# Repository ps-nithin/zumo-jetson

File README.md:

# zumo-jetson

A robot that learns and recognizes patterns on the go.

1. The robot is based on Jetson Nano.

2. The demo script reads the camera frames. Masks the blob, here green (for recognizing) and blue (for learning), using color based segmentation by converting the frames to HSV color space. A check is applied to avoid blobs overlapping with the edge of the frame. The masked image is then inputted to pyrebel which learns/recognizes the blob (using https://github.com/ps-nithin/pyrebel#5-pattern-recognition-demo). Here the recognized symbols are mapped with audio recordings made during learning the pattern. The recorded audio is played back during recognition.

3. The robot uses an Arduino Nano RP2040 Connect as motor controller. It is connected to jetson nano over usb. The arduino firmware has common functions to drive motors and leds connected to it. For example, sending "blinkledwhite_1" over serial to the arduino turns on the white led.

4. Three leds (white, green and blue) connected to the arduino shows the current state of the program. The white led blinks when the program is ready to accept input. The green led blinks when a green blob is detected in the input and the program tries to recognize the input. The blue led blinks when a blue blob is detected in the input and the program tries to learn the input. When both the green and the blue led blinks it indicates that both green and blue blobs are present in the input.

5. A speaker and microphone is connected to jetson nano over usb. A Raspberry pi camera module v2 is connected to csi camera port of the jetson nano. Wireless connectivity nor internet is needed to run the program but is used for setting up jetson nano.

# Patterns
The program can handle both green and blue patterns simultaneously. These different combinations of green and blue patterns can occur,

1. Only green patterns are present in the input.
In this case only recognition happens, either in 'image', or 'audio' channel. Channel having higher weightage is selected.

2. Only blue patterns are present.
In this case only learning happens. Since there are no green patterns, all the learning happens in 'audio' channel only. If there are multiple blue patterns, each constituent blue pattern has to be learned seperately in 'audio' channel before learning the pattern as a whole. 

3. Input contains a combination of green and blue patterns.
In this case both learning and recognition happens. The blue patterns are learned with the symbol recognized from reading the green patterns. Both recognizing green patterns and learning blue patterns takes place in channel 'image'.

# Pre-training
Letters of the English alphabets are pre-trained to provide a vocabulary for learning more complex patterns. The pre-trained letters can be relearned later to update the knowbase with different variations of the pre-trained letters as required. 

# Motors
The motors are controlled by four keywords in channel 'image'. 
1. 'fw' for moving forward.
2. 'bw' for moving backward.
3. 'sc' for spinning in clockwise direction.
4. 'sa' for spinning in anti clockwise direction.

These keywords can be reassigned later to any arbitrary pattern you like by relearning.

# Channels
When an image is learned its signatures are stored in channel 'image'. When a recording is made the signatures are stored in channel 'audio'. During recognition, different symbols may be recognized for each channels. The symbol from channel with higher weightage is selected.

# Build
<p align="center"></img></p><br>

1. Zumo chassis (Pololu - Zumo Chassis Kit (No Motors) https://www.pololu.com/product/1418) act as the main chassis.
2. Motors (Pololu - 298:1 Micro Metal Gearmotor HPCB 6V https://www.pololu.com/product/3069)
3. Motor driver (Pololu - DRV8833 Dual Motor Driver Carrier https://www.pololu.com/product/2130)
4. Voltage regulator (Pololu - 5V Step-Up/Step-Down Voltage Regulator S9V11F5 https://www.pololu.com/product/2836)
5. Arduino Nano RP2040 connect as motor controller
6. Raspberry Pi Camera v2 for camera with acrylic camera mount
7. USB microphone
8. USB speaker
9. USB Wifi dongle / AC8265 Wireless NIC for Jetson Nano for wifi
10. Standoffs and PCBs for structure holding the components
11. Powered by 4xAA batteries.

You could hook up the wires using schematic or there is a robot controller <a href="docs/photo-pcb.jpg">board</a> (please find design files in `docs/zumo-jetson-pcb`).

# Setup
Tested to run on a Jetson Nano with Jetpack 4.6.1.
1. Update packages<br>
`sudo apt update`<br>
`sudo apt upgrade`<br>

2. Install jetson-utils
https://github.com/dusty-nv/jetson-utils

3. Install miniforge with https://github.com/conda-forge/miniforge#unix-like-platforms-macos-linux--wsl<br>
     Numba is installed inside miniforge environment.<br>
     Run the following commands to install numba,<br>
     `source $HOME/miniforge3/bin/activate`<br>
     `conda install python=3.8`<br>
     `conda install -c numba numba`<br>
     
     Copy `jetson-utils` library files from `/usr/lib/python3.6/dist-packages/` to `$HOME/miniforge3/lib/python3.8/site-packages`<br>

     `python3 -m pip install pyserial`<br>
     `python3 -m pip install scipy`<br>
     `python3 -m pip install sounddevice`<br>
     `sudo apt install libportaudio2 espeak-ng`<br>
    
4. Install pyrebel<br>
   `cd`<br>
   `git clone https://github.com/ps-nithin/pyrebel`<br>
   `cd pyrebel`<br>
   `python3 -m pip install .`<br>
   
   Patterns can also be learned using `pyrebel/demo/pyrebel_main_learn_multiple.py` (https://github.com/ps-nithin/pyrebel#5-pattern-recognition-demo).<br>
   For example, images in zumo-jetson/scripts/images/train-hand/ are learned to learn English vocabulary.<br>
   `python3 pyrebel_main_learn_multiple.py --learn images/train-hand/`

You may also need to change the microphone and speaker settings.

# Running the script
1. Demo script 1 - Single pattern<br>
`cd`<br>
`git clone https://github.com/ps-nithin/zumo-jetson`<br>
`cd zumo-jetson/scripts`<br>
`sudo $HOME/miniforge3/bin/python3 pyrebel_main_learn_sound_jetson.py --camera 1 --user=$USERNAME`<br>

2. Demo script 2 - Multiple patterns<br>
`cd`<br>
`git clone https://github.com/ps-nithin/zumo-jetson`<br>
`cd zumo-jetson/scripts`<br>
`sudo $HOME/miniforge3/bin/python3 pyrebel_main_learn_sound_jetson_multiple.py --camera 1 --user=$USERNAME`<br>

# Running the script on startup
`sudo cp zumo-jetson.service /etc/systemd/system/`<br>
`sudo systemctl daemon-reload`<br>
`sudo systemctl enable zumo-jetson.service`<br>
`sudo systemctl start zumo-jetson.service`<br>

If everything went right you should see the white led blinking!

# Demo
1. https://youtu.be/uzXOSZ4ztho Intro
2. https://youtu.be/M06xsy5dlf4 Motor control

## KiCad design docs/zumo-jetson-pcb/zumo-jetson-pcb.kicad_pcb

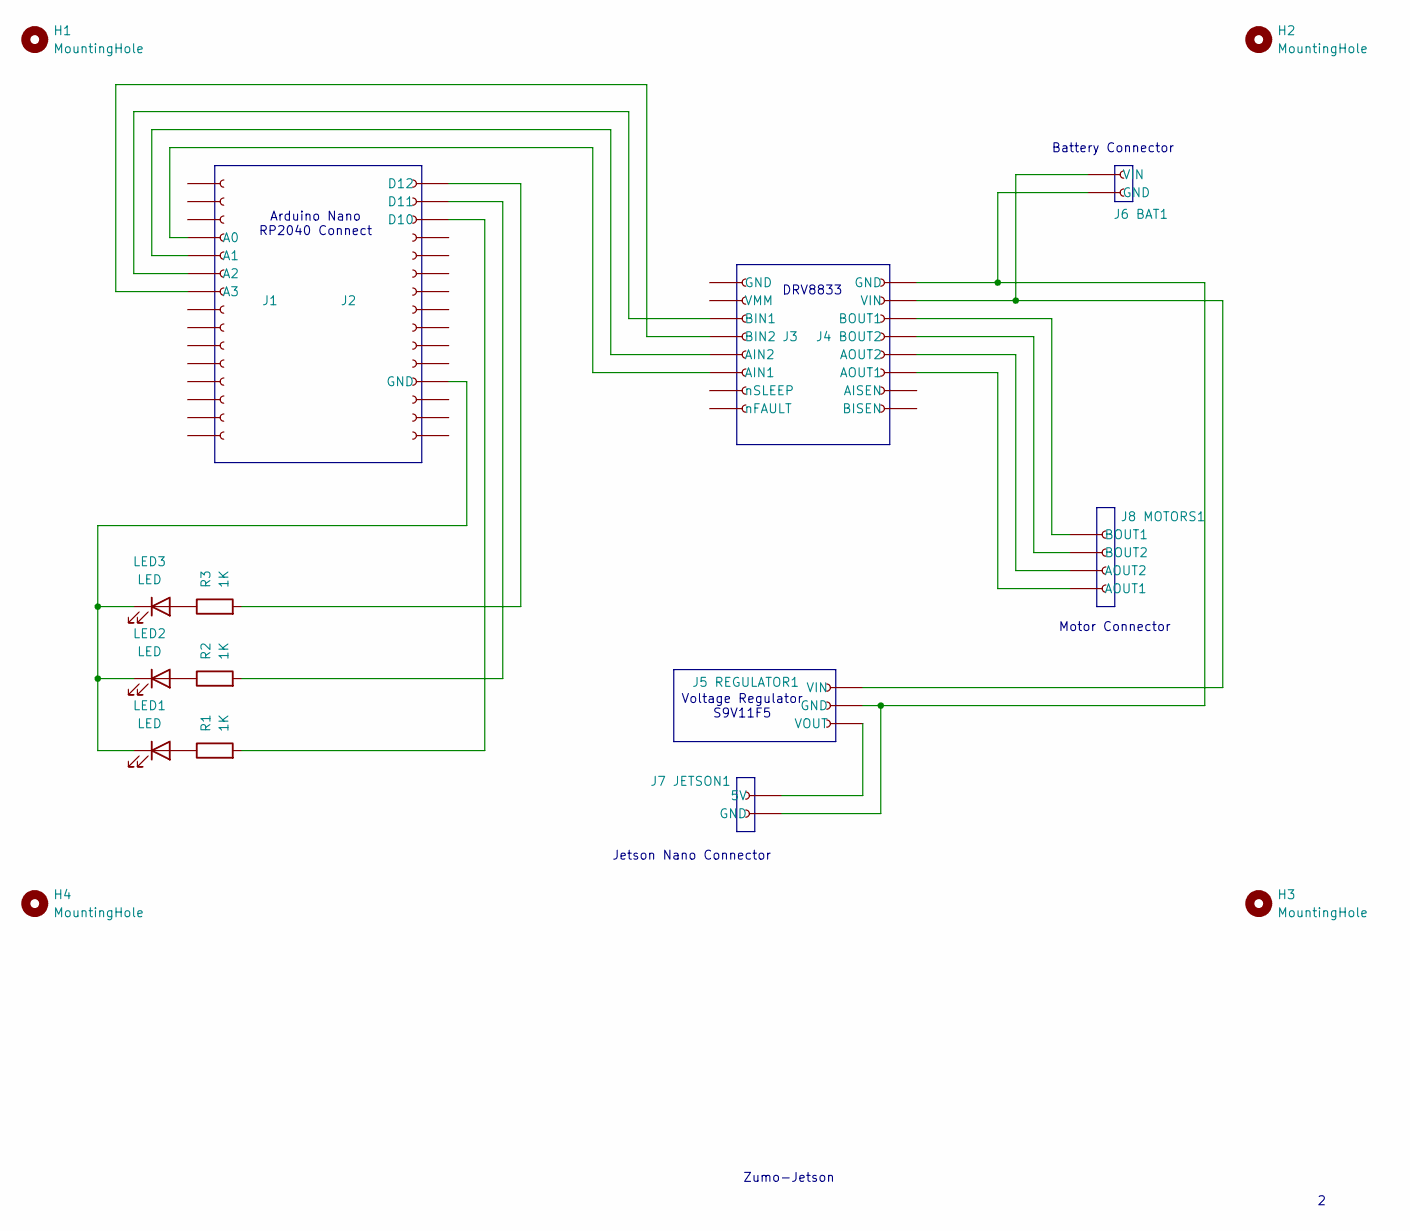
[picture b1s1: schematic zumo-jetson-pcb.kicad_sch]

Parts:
H1, H2, H3, H4: MountingHole; MountingHole_2.7mm_M2.5
J1, J2: Conn_01x15_Socket; PinSocket_1x15_P2.54mm_Vertical
J3, J4: Conn_01x08_Socket; PinSocket_1x08_P2.54mm_Vertical
J5 REGULATOR1: Conn_01x03_Socket; PinSocket_1x03_P2.54mm_Vertical
J6 BAT1, J7 JETSON1: Conn_01x02_Socket; PinHeader_1x02_P2.54mm_Vertical
J8 MOTORS1: Conn_01x04_Socket; PinHeader_1x04_P2.54mm_Vertical
LED1, LED2, LED3: LED; PinSocket_1x02_P2.54mm_Vertical
R1, R2, R3: 1K; R_Axial_DIN0204_L3.6mm_D1.6mm_P2.54mm_Vertical

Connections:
unnamed: J1.4 (A0), J3.6 (AIN1)
unnamed: J1.5 (A1), J3.5 (AIN2)
unnamed: J1.6 (A2), J3.3 (BIN1)
unnamed: J1.7 (A3), J3.4 (BIN2)
unnamed: J2.3 (D10), R1.2
unnamed: J2.2 (D11), R2.2
unnamed: J2.1 (D12), R3.2
unnamed: J2.12 (GND), LED1.1 (K), LED2.1 (K), LED3.1 (K)
unnamed: J4.6 (AOUT1), J8 MOTORS1.4 (AOUT1)
unnamed: J4.5 (AOUT2), J8 MOTORS1.3 (AOUT2)
unnamed: J4.3 (BOUT1), J8 MOTORS1.1 (BOUT1)
unnamed: J4.4 (BOUT2), J8 MOTORS1.2 (BOUT2)
unnamed: J4.1 (GND), J5 REGULATOR1.2 (GND), J6 BAT1.2 (GND), J7 JETSON1.2 (GND)
unnamed: J4.2 (VIN), J5 REGULATOR1.1 (VIN), J6 BAT1.1 (VIN)
unnamed: J5 REGULATOR1.3 (VOUT), J7 JETSON1.1 (5V)
unnamed: LED1.2 (A), R1.1
unnamed: LED2.2 (A), R2.1
unnamed: LED3.2 (A), R3.1

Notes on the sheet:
Arduino Nano RP2040 Connect
Voltage Regulator S9V11F5
Battery Connector
Motor Connector
Zumo-Jetson
Jetson Nano Connector
DRV8833

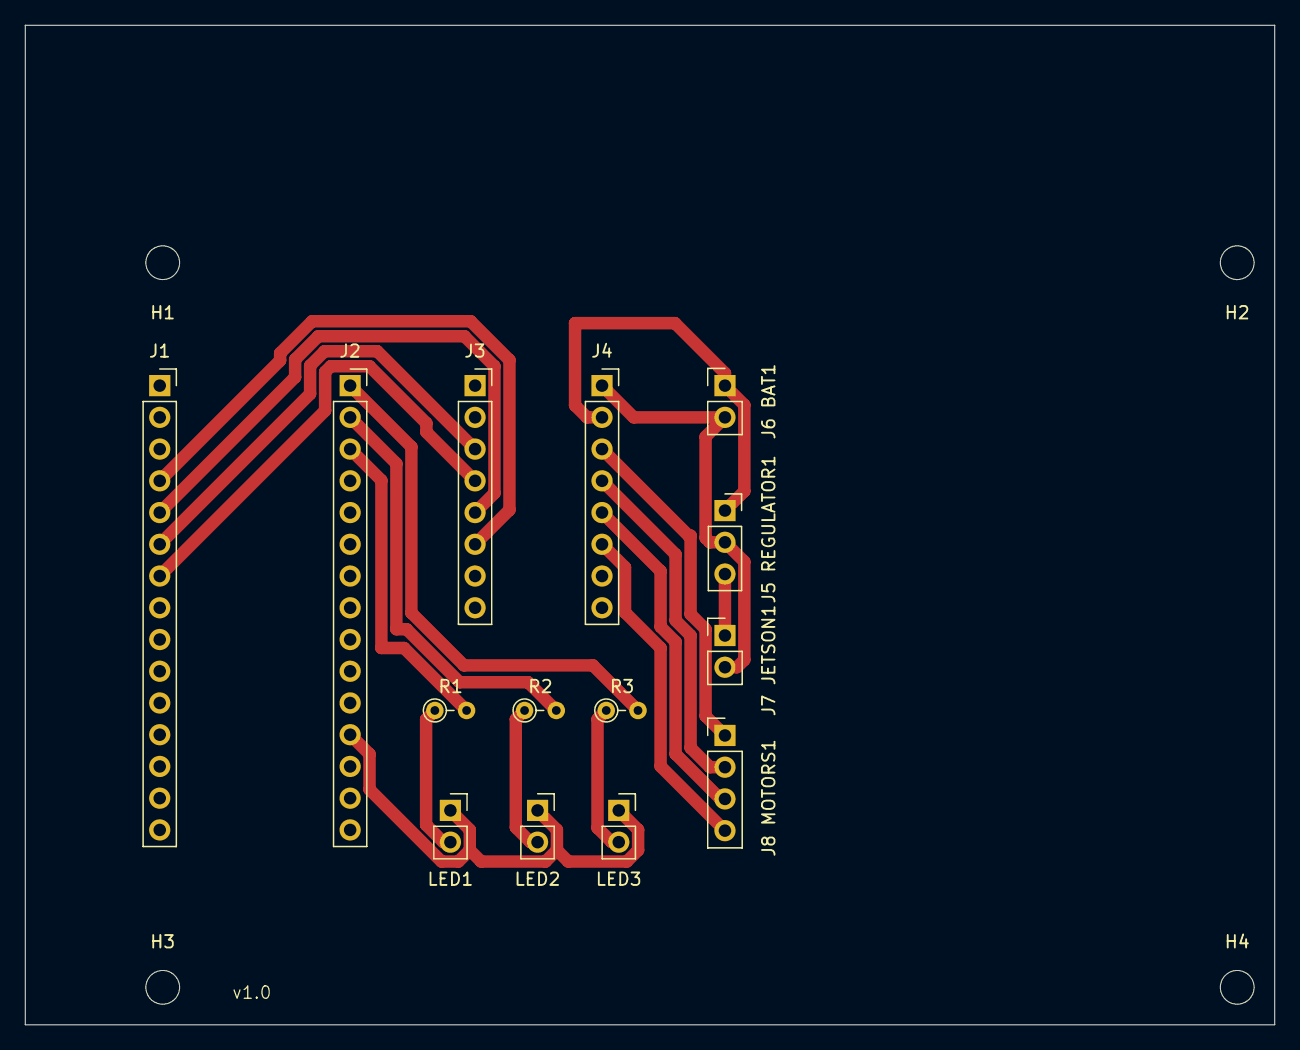
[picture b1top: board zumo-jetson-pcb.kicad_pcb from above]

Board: 2 copper layers, 100.0 x 80.0 mm, 18 parts (0 on the bottom side), 18 nets.

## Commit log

2025-07-04 Create temp
2025-07-21 Minor changes
2025-09-20 Multiple pattern demo.
